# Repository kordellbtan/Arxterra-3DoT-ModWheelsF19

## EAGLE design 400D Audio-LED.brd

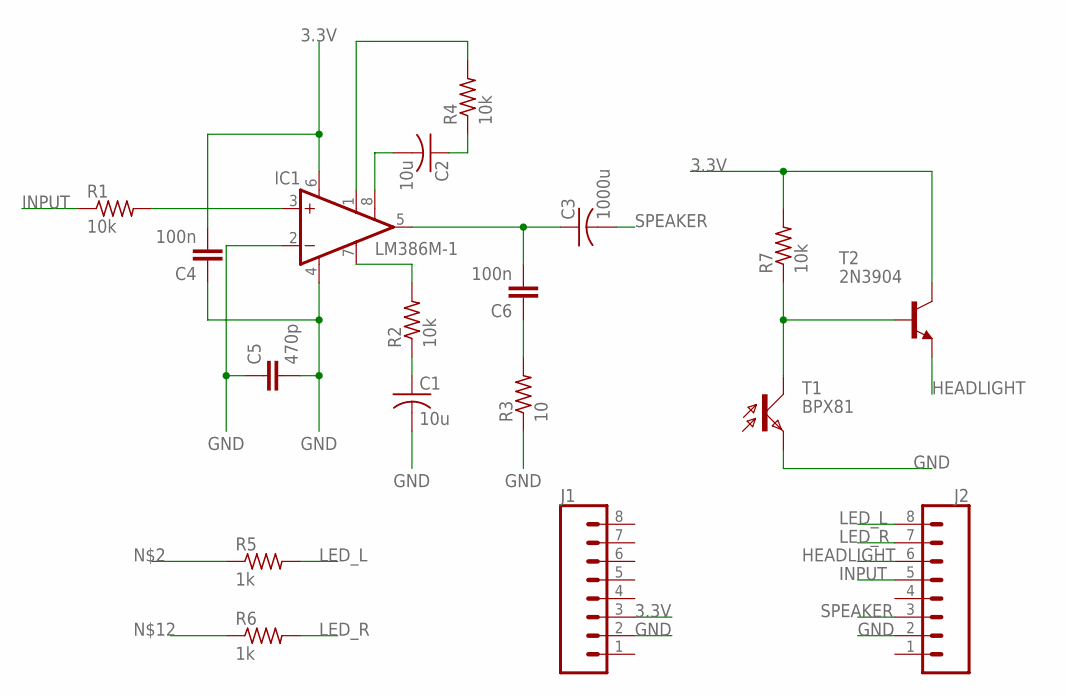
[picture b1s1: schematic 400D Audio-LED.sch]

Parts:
C1, C2: 10u; C0805
C3: 1000u; C0805
C4, C6: 100n; C0805
C5: 470p; C0805
IC1: LM386M-1; SO08
J1, J2: CONN_08"; 1X08
R1, R2, R4, R7: 10k; R0805
R3: 10; R0805
R5, R6: 1k; R0805
T1: BPX81
T2: 2N3904; TO92

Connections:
3.3V: C4.2, IC1.6 (VS), J1.3, R7.2, T2.1 (C)
GND: C1.2, C4.1, C5.1, C5.2, IC1.2 (-IN), IC1.4 (GND), J1.2, J2.2, R3.1, T1.E
HEADLIGHT: J2.6, T2.3 (E)
INPUT: J2.5, R1.1
LED_L: J2.8, R5.2
LED_R: J2.7, R6.2
unnamed: IC1.3 (+IN), R1.2
unnamed: R7.1, T1.C, T2.2 (B)
unnamed: IC1.7 (BYPASS), R2.2
unnamed: C1.1, R2.1
unnamed: C3.1, C6.2, IC1.5 (OUT)
unnamed: C6.1, R3.2
unnamed: C2.2, IC1.8 (GAIN)
unnamed: C2.1, R4.1
unnamed: IC1.1 (GAIN), R4.2
SPEAKER: C3.2, J2.3

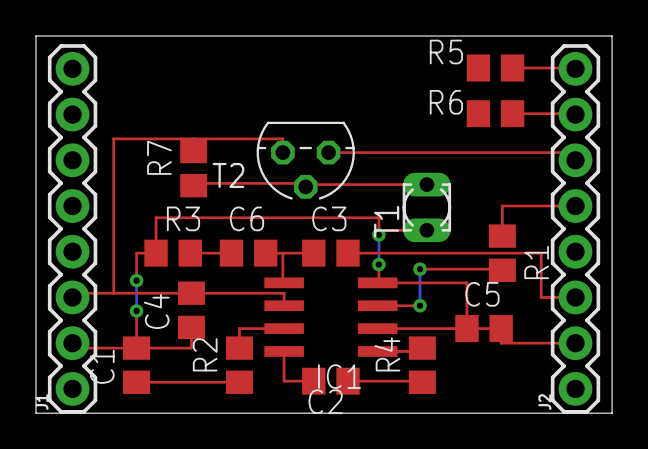
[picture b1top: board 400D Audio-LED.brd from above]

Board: 2 copper layers, 32.0 x 21.0 mm, 18 parts (0 on the bottom side), 16 nets.

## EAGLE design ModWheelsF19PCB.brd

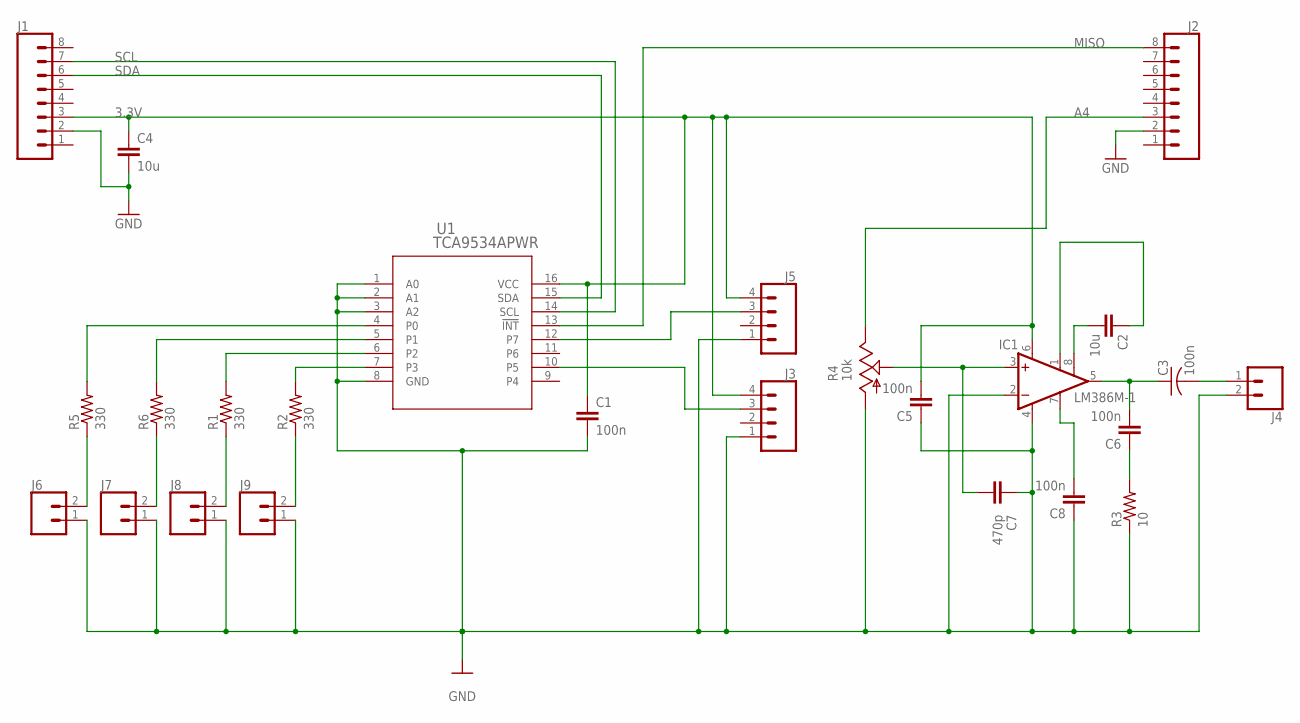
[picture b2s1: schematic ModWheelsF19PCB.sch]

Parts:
C1, C3, C5, C6, C8: 100n; C0805
C2, C4: 10u; C0805
C7: 470p; C0805
IC1: LM386M-1; SO08
J1, J2: CONN_08"; 1X08
J3, J5: CONN_04PTH; 1X04
J4, J6, J7, J8, J9: CONN_02; 1X02
R1, R2, R5, R6: 330; R0805
R3: 10; R0805
R4: 10k; S75P
U1: TCA9534APWR; PW16

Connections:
3.3V: C1.1, C4.1, C5.2, IC1.6 (VS), J1.3, J3.4, J5.4, U1.16 (VCC)
A4: J2.3, R4.E
GND: C1.2, C4.2, C5.1, C7.1, C8.1, IC1.2 (-IN), IC1.4 (GND), J1.2, J2.2, J3.1, J4.2, J5.1, J6.1, J7.1, J8.1, J9.1, R3.1, R4.A, U1.1 (A0), U1.2 (A1), U1.3 (A2), U1.8 (GND)
MISO: J2.8, U1.13 (!INT)
unnamed: C7.2, IC1.3 (+IN), R4.S
unnamed: J6.2, R5.1
unnamed: J9.2, R2.1
unnamed: J8.2, R1.1
unnamed: R6.2, U1.5 (P1)
unnamed: R2.2, U1.7 (P3)
unnamed: C3.1, C6.2, IC1.5 (OUT)
unnamed: C6.1, R3.2
unnamed: C2.2, IC1.8 (GAIN)
unnamed: C2.1, IC1.1 (GAIN)
unnamed: J7.2, R6.1
unnamed: R1.2, U1.6 (P2)
unnamed: R5.2, U1.4 (P0)
unnamed: C8.2, IC1.7 (BYPASS)
unnamed: J3.3, U1.10 (P5)
unnamed: J5.3, U1.12 (P7)
SCL: J1.7, U1.14 (SCL)
SDA: J1.6, U1.15 (SDA)
SPEAKER: C3.2, J4.1

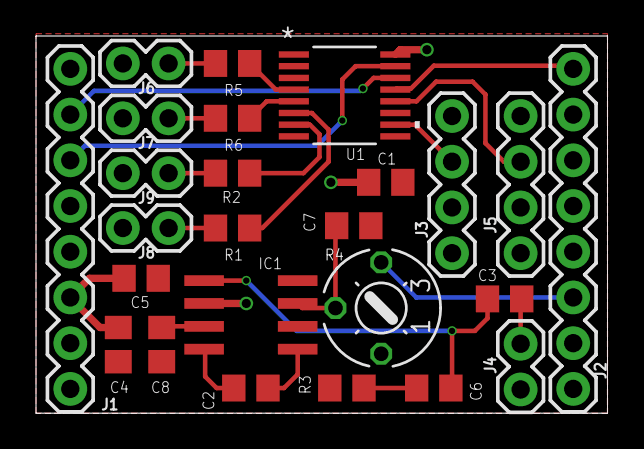
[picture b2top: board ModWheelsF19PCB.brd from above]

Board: 2 copper layers, 31.8 x 21.0 mm, 25 parts (0 on the bottom side), 23 nets.

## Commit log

2020-12-30 pcb board CAD
2020-12-30 pcb board schematic
2020-12-30 chassis laser cut files
2020-12-30 pcb design board-400
2020-12-30 pcb design schematic-400
2020-12-30 CAD file

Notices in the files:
parts and their libraries:
SparkFun-Connectors: Licensing: Creative Commons ShareAlike 4.0 International - https://creativecommons.org/licenses/by-sa/4.0
